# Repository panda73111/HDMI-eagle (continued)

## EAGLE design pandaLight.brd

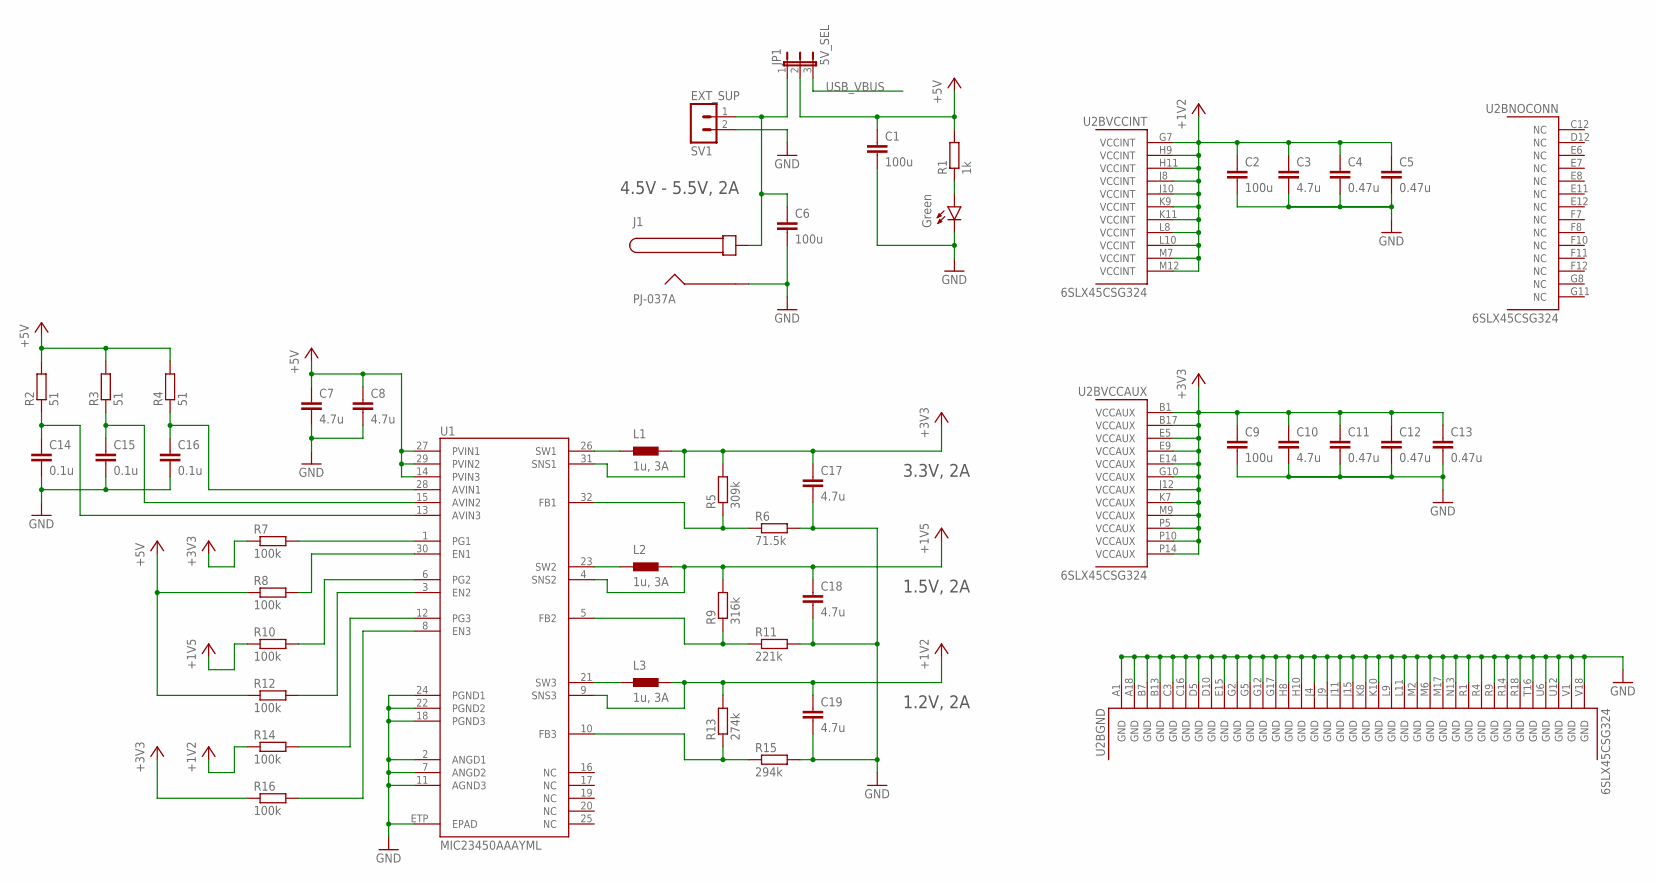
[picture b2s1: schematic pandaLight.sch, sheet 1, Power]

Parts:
C1, C2, C6, C9: 100u; 1206; PARTNO CL31A107MQHNNNE
C3, C7, C8, C10, C17, C18, C19: 4.7u; 0603; PARTNO C0603C475K9PACTU
C4, C5, C11, C12, C13: 0.47u; 0402; PARTNO C1005X5R0J474K050BB
C14, C15, C16: 0.1u; 0402; PARTNO CL05B104KP5NNNC
J1: PJ-037A; PARTNO PJ-037A
JP1: 5V_SEL; JP2; PARTNO *
L1, L2, L3: 1u, 3A; 1008; PARTNO CIG22E1R0MNE
LED1: Green; LED-0603; PARTNO LG Q971-KN-1
R1: 1k; 0402; PARTNO ERJ-2RKF1001X
R2, R3, R4: 51; 0402; PARTNO ERJ-2RKF51R0X
R5: 309k; 0402; PARTNO ERJ-2RKF3093X
R6: 71.5k; 0402; PARTNO ERJ-2RKF7152X
R7, R8, R10, R12, R14, R16: 100k; 0402; PARTNO ERJ-2RKF1003X
R9: 316k; 0402; PARTNO ERJ-2RKF3163X
R11: 221k; 0402; PARTNO ERJ-2RKF2213X
R13: 274k; 0402; PARTNO ERJ-2RKF2743X
R15: 294k; 0402; PARTNO ERJ-2RKF2943X
SV1: EXT_SUP; MA02-1; PARTNO *
U1: MIC23450AAAYML; QFN-32-5X5; PARTNO MIC23450-AAAYML TR
U2: 6SLX45CSG324; CS324; PARTNO XC6SLX45-3CSG324C

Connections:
+1V2: C2.1, C3.1, C4.1, C5.1, C19.1, L3.2, R13.2, R14.1, U1.9 (SNS3), U2.G7 (VCCINT), U2.H9 (VCCINT), U2.H11 (VCCINT), U2.J8 (VCCINT), U2.J10 (VCCINT), U2.K9 (VCCINT), U2.K11 (VCCINT), U2.L8 (VCCINT), U2.L10 (VCCINT), U2.M7 (VCCINT), U2.M12 (VCCINT)
+1V5: C18.1, L2.2, R9.2, R10.1, U1.4 (SNS2); also elsewhere on the board
+3V3: C9.1, C10.1, C11.1, C12.1, C13.1, C17.1, L1.2, R5.2, R7.1, R16.1, U1.31 (SNS1), U2.B1 (VCCAUX), U2.B17 (VCCAUX), U2.E5 (VCCAUX), U2.E9 (VCCAUX), U2.E14 (VCCAUX), U2.G10 (VCCAUX), U2.J12 (VCCAUX), U2.K7 (VCCAUX), U2.M9 (VCCAUX), U2.P5 (VCCAUX), U2.P10 (VCCAUX), U2.P14 (VCCAUX); also elsewhere on the board
+5V: C1.1, C7.1, C8.1, JP1.2, R1.2, R2.2, R3.2, R4.2, R8.1, R12.1, U1.14 (PVIN3), U1.27 (PVIN1), U1.29 (PVIN2); also elsewhere on the board
CENTER: C6.1, J1.CENTER, JP1.1, SV1.1
GND: C1.2, C2.2, C3.2, C4.2, C5.2, C6.2, C7.2, C8.2, C9.2, C10.2, C11.2, C12.2, C13.2, C14.2, C15.2, C16.2, C17.2, C18.2, C19.2, J1.BARREL, LED1.C, R6.2, R11.2, R15.2, SV1.2, U1.2 (ANGD1), U1.7 (ANGD2), U1.11 (AGND3), U1.18 (PGND3), U1.22 (PGND2), U1.24 (PGND1), U1.ETP (EPAD), U2.A1 (GND), U2.A18 (GND), U2.B7 (GND), U2.B13 (GND), U2.C3 (GND), U2.C16 (GND), U2.D5 (GND), U2.D10 (GND), U2.E15 (GND), U2.G2 (GND), U2.G5 (GND), U2.G12 (GND), U2.G17 (GND), U2.H8 (GND), U2.H10 (GND), U2.J4 (GND), U2.J9 (GND), U2.J11 (GND), U2.J15 (GND), U2.K8 (GND), U2.K10 (GND), U2.L9 (GND), U2.L11 (GND), U2.M2 (GND), U2.M6 (GND), U2.M17 (GND), U2.N13 (GND), U2.R1 (GND), U2.R4 (GND), U2.R9 (GND), U2.R14 (GND), U2.R18 (GND), U2.T16 (GND), U2.U6 (GND), U2.U12 (GND), U2.V1 (GND), U2.V18 (GND); also elsewhere on the board
unnamed: L1.1, U1.26 (SW1)
unnamed: C16.1, R4.1, U1.28 (AVIN1)
unnamed: L2.1, U1.23 (SW2)
unnamed: L3.1, U1.21 (SW3)
unnamed: R13.1, R15.1, U1.10 (FB3)
unnamed: R10.2, U1.6 (PG2)
unnamed: R5.1, R6.1, U1.32 (FB1)
unnamed: R7.2, U1.1 (PG1)
unnamed: R9.1, R11.1, U1.5 (FB2)
unnamed: R12.2, U1.3 (EN2)
unnamed: R8.2, U1.30 (EN1)
unnamed: R14.2, U1.12 (PG3)
unnamed: R16.2, U1.8 (EN3)
unnamed: C15.1, R3.1, U1.15 (AVIN2)
unnamed: LED1.A, R1.1
unnamed: C14.1, R2.1, U1.13 (AVIN3)
USB_VBUS: JP1.3; also elsewhere on the board

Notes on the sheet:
4.5V - 5.5V, 2A
3.3V, 2A
1.5V, 2A
1.2V, 2A

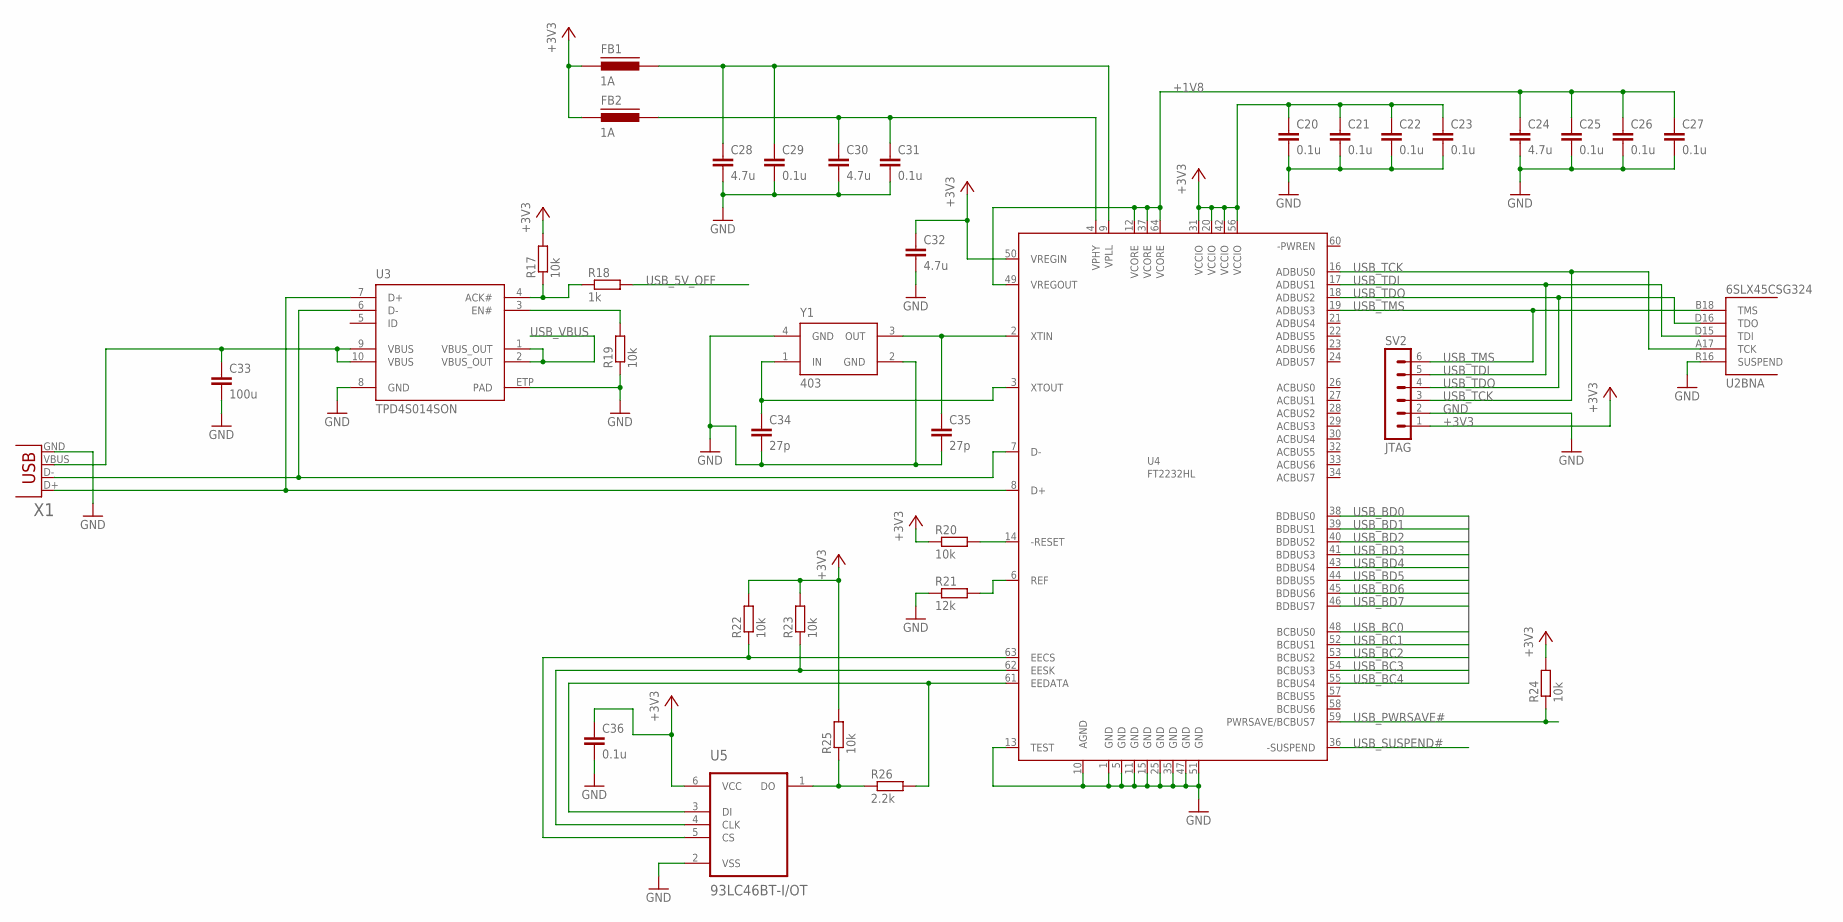
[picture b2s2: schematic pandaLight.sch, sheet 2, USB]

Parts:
C20, C21, C22, C23, C25, C26, C27, C29, C31, C36: 0.1u; 0402; PARTNO CL05B104KP5NNNC
C24, C28, C30, C32: 4.7u; 0603; PARTNO C0603C475K9PACTU
C33: 100u; 1206; PARTNO CL31A107MQHNNNE
C34, C35: 27p; 0402; PARTNO CL05C270JB5NNNC
FB1, FB2: 1A; 0402; PARTNO BK1005HS100-T
R17, R19, R20, R22, R23, R24, R25: 10k; 0402; PARTNO ERJ-2RKF1002X
R18: 1k; 0402; PARTNO ERJ-2RKF1001X
R21: 12k; 0402; PARTNO ERJ-2RKF1202X
R26: 2.2k; 0402; PARTNO ERJ-2RKF2201X
SV2: JTAG; MA06-1; PARTNO *
U2: 6SLX45CSG324; CS324; PARTNO XC6SLX45-3CSG324C
U3: TPD4S014SON; SON10; PARTNO TPD4S014DSQR
U4: FT2232HL; LQFP64; PARTNO FT2232HL-REEL
U5: 93LC46BT-I/OT; SOT23-6; PARTNO 93LC46BT-I/OT
X1: USBUB-S; USB-UB-S; PARTNO 10118192-0001LF
Y1: 403; 403-3.2X2.5; PARTNO 403C35D12M00000

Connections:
+1V8: C24.1, C25.1, C26.1, C27.1, U4.12 (VCORE), U4.37 (VCORE), U4.49 (VREGOUT), U4.64 (VCORE)
+3V3: C20.1, C21.1, C22.1, C23.1, C32.1, C36.1, FB1.1, FB2.1, R17.2, R20.1, R22.2, R23.2, R24.2, R25.2, SV2.1, U4.20 (VCCIO), U4.31 (VCCIO), U4.42 (VCCIO), U4.50 (VREGIN), U4.56 (VCCIO), U5.6 (VCC); also elsewhere on the board
GND: C20.2, C21.2, C22.2, C23.2, C24.2, C25.2, C26.2, C27.2, C28.2, C29.2, C30.2, C31.2, C32.2, C33.2, C34.2, C35.2, C36.2, R19.1, R21.1, SV2.2, U2.R16 (SUSPEND), U3.8 (GND), U3.ETP (PAD), U4.1 (GND), U4.5 (GND), U4.10 (AGND), U4.11 (GND), U4.13 (TEST), U4.15 (GND), U4.25 (GND), U4.35 (GND), U4.47 (GND), U4.51 (GND), U5.2 (VSS), X1.GND, Y1.2 (GND), Y1.4 (GND); also elsewhere on the board
unnamed: C35.1, U4.2 (XTIN), Y1.3 (OUT)
unnamed: C34.1, U4.3 (XTOUT), Y1.1 (IN)
unnamed: R22.1, U4.63 (EECS), U5.5 (CS)
unnamed: U3.6 (D-), U4.7 (D-), X1.D-
unnamed: U3.7 (D+), U4.8 (D+), X1.D+
unnamed: R23.1, U4.62 (EESK), U5.4 (CLK)
unnamed: R26.2, U4.61 (EEDATA), U5.3 (DI)
unnamed: R21.2, U4.6 (REF)
unnamed: R25.1, R26.1, U5.1 (DO)
unnamed: R20.2, U4.14 (-RESET)
unnamed: C30.1, C31.1, FB2.2, U4.4 (VPHY)
unnamed: C28.1, C29.1, FB1.2, U4.9 (VPLL)
unnamed: C33.1, U3.9 (VBUS), U3.10 (VBUS), X1.VBUS
USB_5V_ACK#: R17.1, R18.1, U3.4 (ACK#)
USB_5V_DISABLE: R19.2, U3.3 (EN#)
USB_5V_OFF: R18.2
USB_BC0: U4.48 (BCBUS0)
USB_BC1: U4.52 (BCBUS1)
USB_BC2: U4.53 (BCBUS2)
USB_BC3: U4.54 (BCBUS3)
USB_BC4: U4.55 (BCBUS4)
USB_BD0: U4.38 (BDBUS0)
USB_BD1: U4.39 (BDBUS1)
USB_BD2: U4.40 (BDBUS2)
USB_BD3: U4.41 (BDBUS3)
USB_BD4: U4.43 (BDBUS4)
USB_BD5: U4.44 (BDBUS5)
USB_BD6: U4.45 (BDBUS6)
USB_BD7: U4.46 (BDBUS7)
USB_PWRSAVE#: R24.1, U4.59 (PWRSAVE/BCBUS7)
USB_SUSPEND#: U4.36 (-SUSPEND)
USB_TCK: SV2.3, U2.A17 (TCK), U4.16 (ADBUS0)
USB_TDI: SV2.5, U2.D15 (TDI), U4.17 (ADBUS1)
USB_TDO: SV2.4, U2.D16 (TDO), U4.18 (ADBUS2)
USB_TMS: SV2.6, U2.B18 (TMS), U4.19 (ADBUS3)
USB_VBUS: U3.1 (VBUS_OUT), U3.2 (VBUS_OUT); also elsewhere on the board

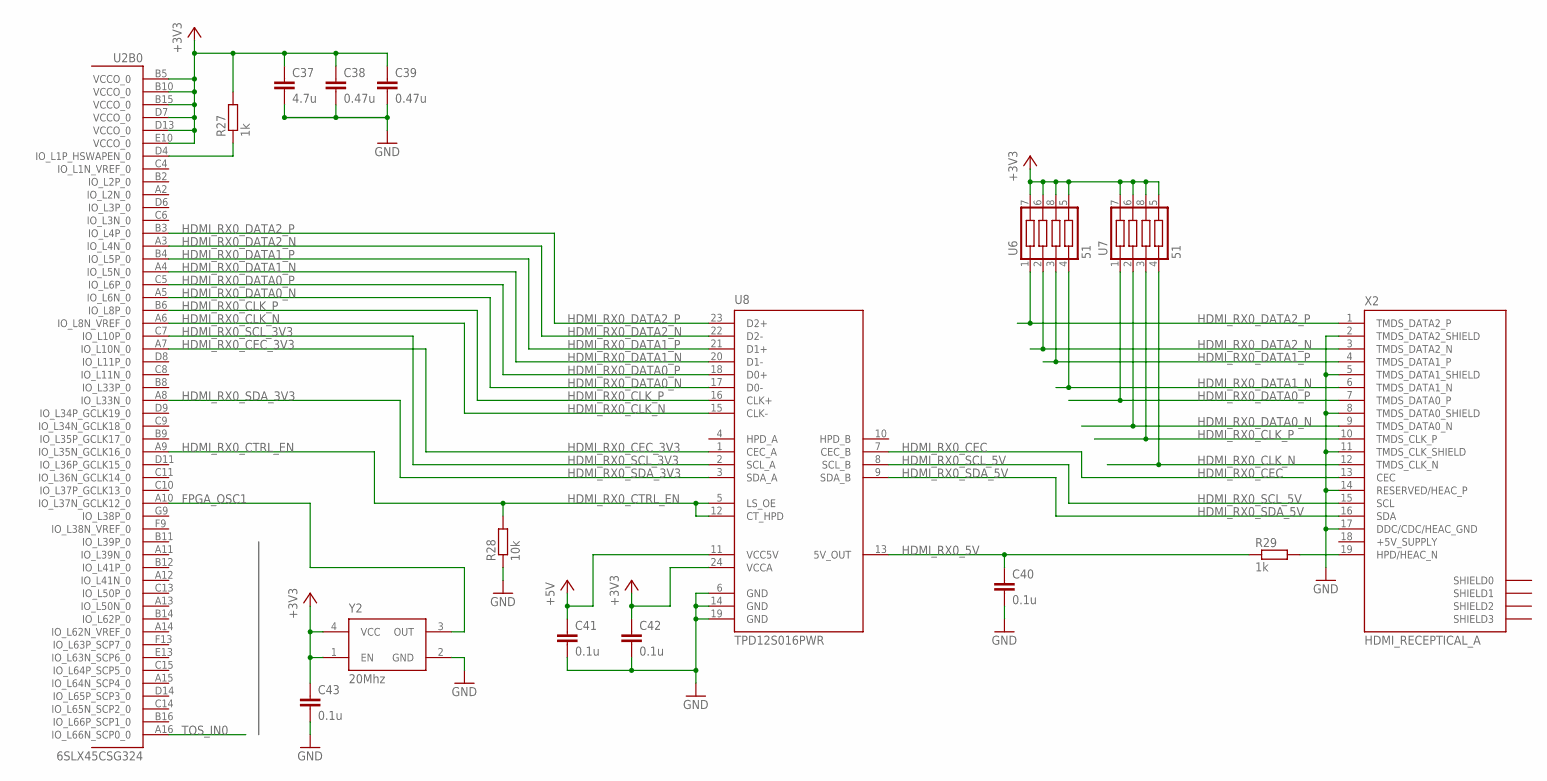
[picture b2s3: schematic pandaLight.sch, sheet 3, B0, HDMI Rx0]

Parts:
C37: 4.7u; 0603; PARTNO C0603C475K9PACTU
C38, C39: 0.47u; 0402; PARTNO C1005X5R0J474K050BB
C40, C41, C42, C43: 0.1u; 0402; PARTNO CL05B104KP5NNNC
R27, R29: 1k; 0402; PARTNO ERJ-2RKF1001X
R28: 10k; 0402; PARTNO ERJ-2RKF1002X
U2: 6SLX45CSG324; CS324; PARTNO XC6SLX45-3CSG324C
U6, U7: 51; 741C083; PARTNO 741C083510JP
U8: TPD12S016PWR; PW_R-PDSO-G24; PARTNO TPD12S016PWR
X2: HDMI_RECEPTICAL_A; HDMI_TYPE_A_RECEPTICAL; PARTNO 10029449-111RLF
Y2: 20Mhz; 636; PARTNO 636L3C020M00000

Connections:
+3V3: C37.1, C38.1, C39.1, C42.1, C43.1, R27.2, U2.B5 (VCCO_0), U2.B10 (VCCO_0), U2.B15 (VCCO_0), U2.D7 (VCCO_0), U2.D13 (VCCO_0), U2.E10 (VCCO_0), U6.5 (13), U6.6 (15), U6.7 (16), U6.8 (C3), U7.5 (13), U7.6 (15), U7.7 (16), U7.8 (C3), U8.24 (VCCA), Y2.1 (EN), Y2.4 (VCC); also elsewhere on the board
+5V: C41.1, U8.11 (VCC5V); also elsewhere on the board
FPGA_OSC1: U2.A10 (IO_L37N_GCLK12_0), Y2.3 (OUT)
GND: C37.2, C38.2, C39.2, C40.2, C41.2, C42.2, C43.2, R28.1, U8.6 (GND), U8.14 (GND), U8.19 (GND), X2.2 (TMDS_DATA2_SHIELD), X2.5 (TMDS_DATA1_SHIELD), X2.8 (TMDS_DATA0_SHIELD), X2.11 (TMDS_CLK_SHIELD), X2.14 (RESERVED/HEAC_P), X2.17 (DDC/CDC/HEAC_GND), Y2.2 (GND); also elsewhere on the board
HDMI_RX0_5V: C40.1, R29.1, U8.13 (5V_OUT)
HDMI_RX0_CEC: U8.7 (CEC_B), X2.13 (CEC)
HDMI_RX0_CEC_3V3: U2.A7 (IO_L10N_0), U8.1 (CEC_A)
HDMI_RX0_CLK_N: U2.A6 (IO_L8N_VREF_0), U7.4, U8.15 (CLK-), X2.12 (TMDS_CLK_N)
HDMI_RX0_CLK_P: U2.B6 (IO_L8P_0), U7.3, U8.16 (CLK+), X2.10 (TMDS_CLK_P)
HDMI_RX0_CTRL_EN: R28.2, U2.A9 (IO_L35N_GCLK16_0), U8.5 (LS_OE), U8.12 (CT_HPD)
HDMI_RX0_DATA0_N: U2.A5 (IO_L6N_0), U7.2, U8.17 (D0-), X2.9 (TMDS_DATA0_N)
HDMI_RX0_DATA0_P: U2.C5 (IO_L6P_0), U7.1, U8.18 (D0+), X2.7 (TMDS_DATA0_P)
HDMI_RX0_DATA1_N: U2.A4 (IO_L5N_0), U6.4, U8.20 (D1-), X2.6 (TMDS_DATA1_N)
HDMI_RX0_DATA1_P: U2.B4 (IO_L5P_0), U6.3, U8.21 (D1+), X2.4 (TMDS_DATA1_P)
HDMI_RX0_DATA2_N: U2.A3 (IO_L4N_0), U6.2, U8.22 (D2-), X2.3 (TMDS_DATA2_N)
HDMI_RX0_DATA2_P: U2.B3 (IO_L4P_0), U6.1, U8.23 (D2+), X2.1 (TMDS_DATA2_P)
HDMI_RX0_SCL_3V3: U2.C7 (IO_L10P_0), U8.2 (SCL_A)
HDMI_RX0_SCL_5V: U8.8 (SCL_B), X2.15 (SCL)
HDMI_RX0_SDA_3V3: U2.A8 (IO_L33N_0), U8.3 (SDA_A)
HDMI_RX0_SDA_5V: U8.9 (SDA_B), X2.16 (SDA)
unnamed: R27.1, U2.D4 (IO_L1P_HSWAPEN_0)
unnamed: R29.2, X2.19 (HPD/HEAC_N)
TOS_IN0: U2.A16 (IO_L66N_SCP0_0); also elsewhere on the board

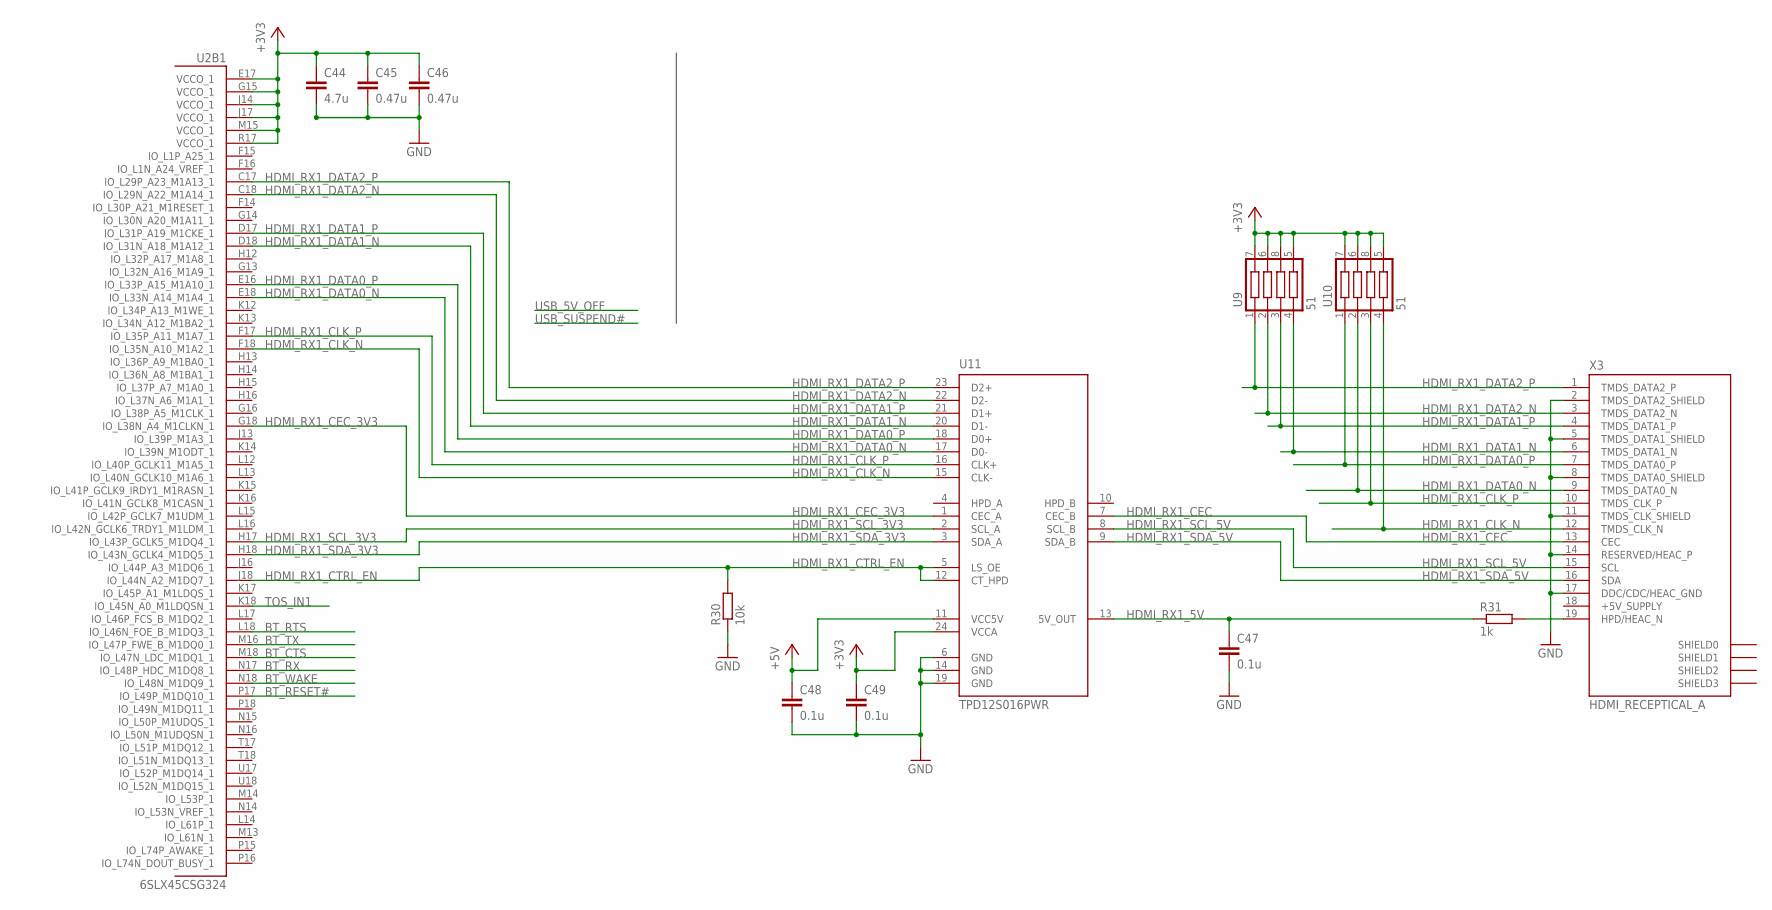
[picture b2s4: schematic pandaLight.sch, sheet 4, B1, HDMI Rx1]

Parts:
C44: 4.7u; 0603; PARTNO C0603C475K9PACTU
C45, C46: 0.47u; 0402; PARTNO C1005X5R0J474K050BB
C47, C48, C49: 0.1u; 0402; PARTNO CL05B104KP5NNNC
R30: 10k; 0402; PARTNO ERJ-2RKF1002X
R31: 1k; 0402; PARTNO ERJ-2RKF1001X
U2: 6SLX45CSG324; CS324; PARTNO XC6SLX45-3CSG324C
U9, U10: 51; 741C083; PARTNO 741C083510JP
U11: TPD12S016PWR; PW_R-PDSO-G24; PARTNO TPD12S016PWR
X3: HDMI_RECEPTICAL_A; HDMI_TYPE_A_RECEPTICAL; PARTNO 10029449-111RLF

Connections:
+3V3: C44.1, C45.1, C46.1, C49.1, U2.E17 (VCCO_1), U2.G15 (VCCO_1), U2.J14 (VCCO_1), U2.J17 (VCCO_1), U2.M15 (VCCO_1), U2.R17 (VCCO_1), U9.5 (13), U9.6 (15), U9.7 (16), U9.8 (C3), U10.5 (13), U10.6 (15), U10.7 (16), U10.8 (C3), U11.24 (VCCA); also elsewhere on the board
+5V: C48.1, U11.11 (VCC5V); also elsewhere on the board
BT_CTS: U2.M18 (IO_L47N_LDC_M1DQ1_1); also elsewhere on the board
BT_RESET#: U2.P17 (IO_L49P_M1DQ10_1); also elsewhere on the board
BT_RTS: U2.L18 (IO_L46N_FOE_B_M1DQ3_1); also elsewhere on the board
BT_RX: U2.N17 (IO_L48P_HDC_M1DQ8_1); also elsewhere on the board
BT_TX: U2.M16 (IO_L47P_FWE_B_M1DQ0_1); also elsewhere on the board
BT_WAKE: U2.N18 (IO_L48N_M1DQ9_1); also elsewhere on the board
GND: C44.2, C45.2, C46.2, C47.2, C48.2, C49.2, R30.1, U11.6 (GND), U11.14 (GND), U11.19 (GND), X3.2 (TMDS_DATA2_SHIELD), X3.5 (TMDS_DATA1_SHIELD), X3.8 (TMDS_DATA0_SHIELD), X3.11 (TMDS_CLK_SHIELD), X3.14 (RESERVED/HEAC_P), X3.17 (DDC/CDC/HEAC_GND); also elsewhere on the board
HDMI_RX1_5V: C47.1, R31.1, U11.13 (5V_OUT)
HDMI_RX1_CEC: U11.7 (CEC_B), X3.13 (CEC)
HDMI_RX1_CEC_3V3: U2.G18 (IO_L38N_A4_M1CLKN_1), U11.1 (CEC_A)
HDMI_RX1_CLK_N: U2.F18 (IO_L35N_A10_M1A2_1), U10.4, U11.15 (CLK-), X3.12 (TMDS_CLK_N)
HDMI_RX1_CLK_P: U2.F17 (IO_L35P_A11_M1A7_1), U10.3, U11.16 (CLK+), X3.10 (TMDS_CLK_P)
HDMI_RX1_CTRL_EN: R30.2, U2.J18 (IO_L44N_A2_M1DQ7_1), U11.5 (LS_OE), U11.12 (CT_HPD)
HDMI_RX1_DATA0_N: U2.E18 (IO_L33N_A14_M1A4_1), U10.2, U11.17 (D0-), X3.9 (TMDS_DATA0_N)
HDMI_RX1_DATA0_P: U2.E16 (IO_L33P_A15_M1A10_1), U10.1, U11.18 (D0+), X3.7 (TMDS_DATA0_P)
HDMI_RX1_DATA1_N: U2.D18 (IO_L31N_A18_M1A12_1), U9.4, U11.20 (D1-), X3.6 (TMDS_DATA1_N)
HDMI_RX1_DATA1_P: U2.D17 (IO_L31P_A19_M1CKE_1), U9.3, U11.21 (D1+), X3.4 (TMDS_DATA1_P)
HDMI_RX1_DATA2_N: U2.C18 (IO_L29N_A22_M1A14_1), U9.2, U11.22 (D2-), X3.3 (TMDS_DATA2_N)
HDMI_RX1_DATA2_P: U2.C17 (IO_L29P_A23_M1A13_1), U9.1, U11.23 (D2+), X3.1 (TMDS_DATA2_P)
HDMI_RX1_SCL_3V3: U2.H17 (IO_L43P_GCLK5_M1DQ4_1), U11.2 (SCL_A)
HDMI_RX1_SCL_5V: U11.8 (SCL_B), X3.15 (SCL)
HDMI_RX1_SDA_3V3: U2.H18 (IO_L43N_GCLK4_M1DQ5_1), U11.3 (SDA_A)
HDMI_RX1_SDA_5V: U11.9 (SDA_B), X3.16 (SDA)
unnamed: R31.2, X3.19 (HPD/HEAC_N)
TOS_IN1: U2.K18 (IO_L45N_A0_M1LDQSN_1); also elsewhere on the board

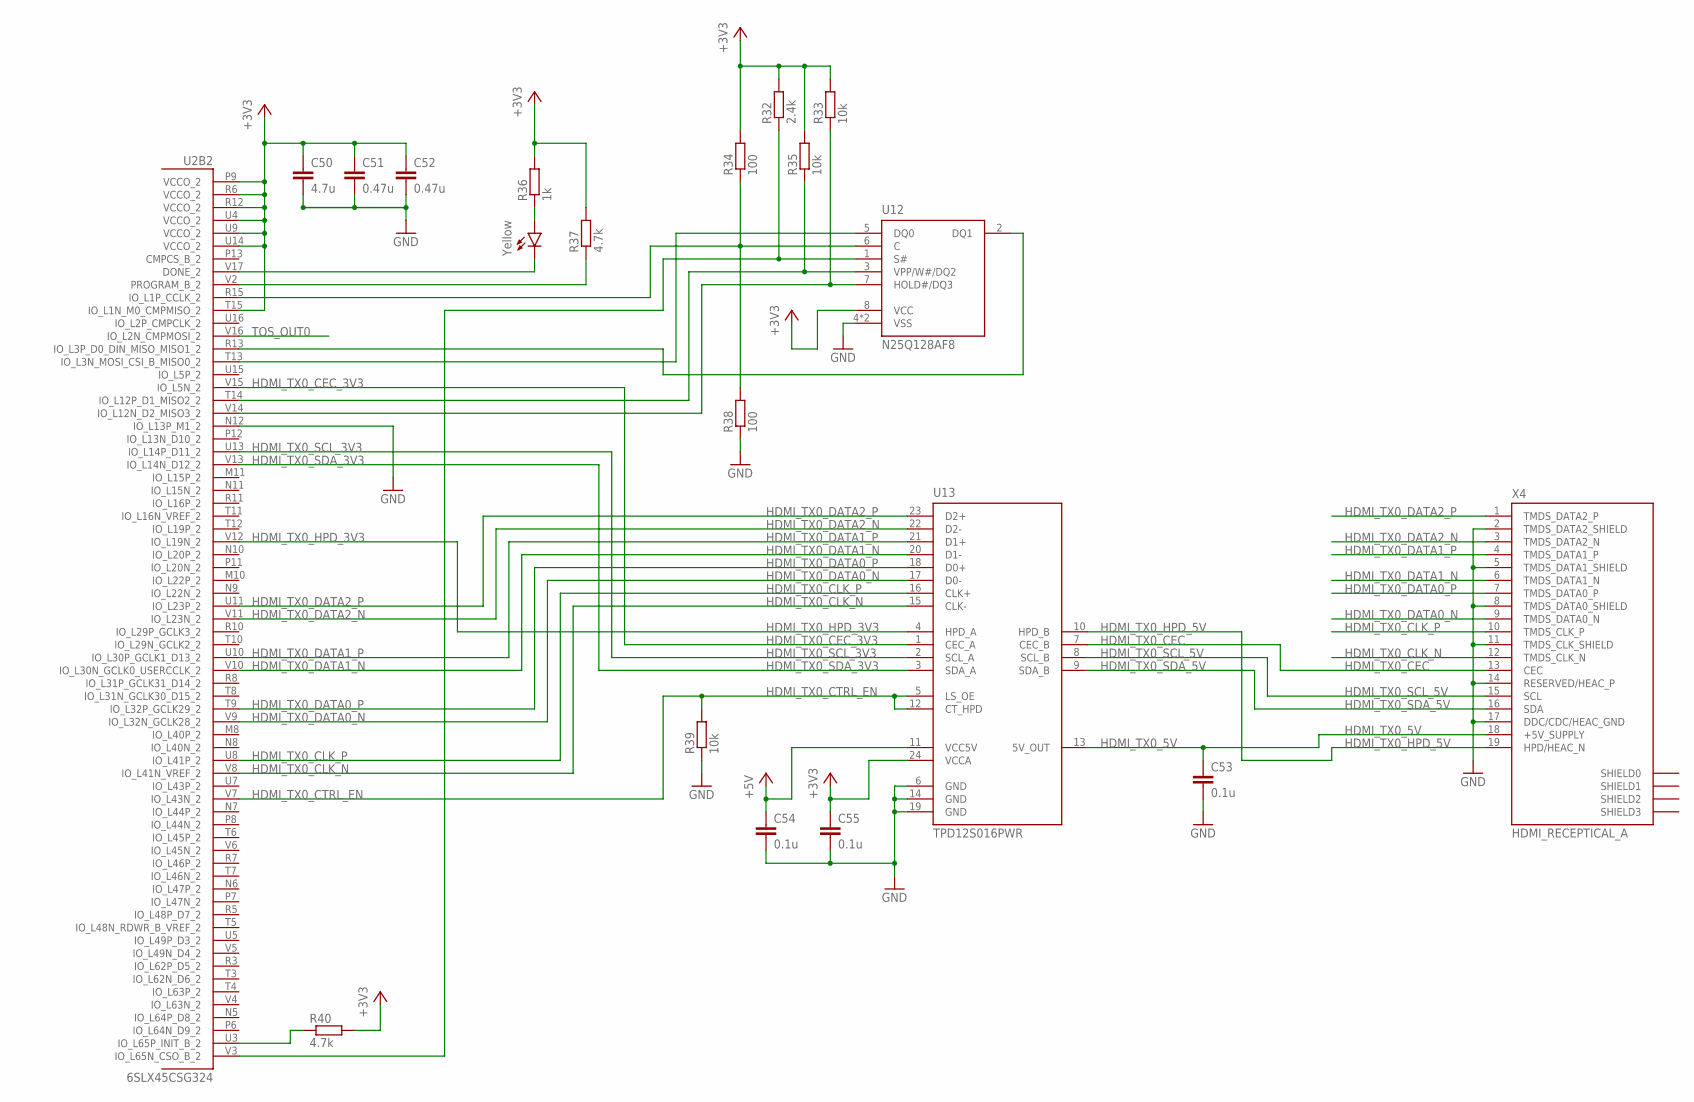
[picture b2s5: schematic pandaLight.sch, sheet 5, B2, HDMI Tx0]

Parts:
C50: 4.7u; 0603; PARTNO C0603C475K9PACTU
C51, C52: 0.47u; 0402; PARTNO C1005X5R0J474K050BB
C53, C54, C55: 0.1u; 0402; PARTNO CL05B104KP5NNNC
LED2: Yellow; LED-0603; PARTNO LY Q976-P1S2-36
R32: 2.4k; 0402; PARTNO ERJ-2RKF2401X
R33, R35, R39: 10k; 0402; PARTNO ERJ-2RKF1002X
R34, R38: 100; 0402; PARTNO ERJ-2GEJ101X
R36: 1k; 0402; PARTNO ERJ-2RKF1001X
R37, R40: 4.7k; 0402; PARTNO ERJ-2RKF4701X
U2: 6SLX45CSG324; CS324; PARTNO XC6SLX45-3CSG324C
U12: N25Q128AF8; V-PDFN-8_8X6; PARTNO N25Q128A13EF840E
U13: TPD12S016PWR; PW_R-PDSO-G24; PARTNO TPD12S016PWR
X4: HDMI_RECEPTICAL_A; HDMI_TYPE_A_RECEPTICAL; PARTNO 10029449-111RLF

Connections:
+3V3: C50.1, C51.1, C52.1, C55.1, R32.2, R33.2, R34.2, R35.2, R36.2, R37.2, R40.2, U2.P9 (VCCO_2), U2.R6 (VCCO_2), U2.R12 (VCCO_2), U2.T15 (IO_L1N_M0_CMPMISO_2), U2.U4 (VCCO_2), U2.U9 (VCCO_2), U2.U14 (VCCO_2), U12.8 (VCC), U13.24 (VCCA); also elsewhere on the board
+5V: C54.1, U13.11 (VCC5V); also elsewhere on the board
GND: C50.2, C51.2, C52.2, C53.2, C54.2, C55.2, R38.1, R39.1, U2.N12 (IO_L13P_M1_2), U12.4 (VSS), U12.ETP (VSS), U13.6 (GND), U13.14 (GND), U13.19 (GND), X4.2 (TMDS_DATA2_SHIELD), X4.5 (TMDS_DATA1_SHIELD), X4.8 (TMDS_DATA0_SHIELD), X4.11 (TMDS_CLK_SHIELD), X4.14 (RESERVED/HEAC_P), X4.17 (DDC/CDC/HEAC_GND); also elsewhere on the board
HDMI_TX0_5V: C53.1, U13.13 (5V_OUT), X4.18 (+5V_SUPPLY)
HDMI_TX0_CEC: U13.7 (CEC_B), X4.13 (CEC)
HDMI_TX0_CEC_3V3: U2.V15 (IO_L5N_2), U13.1 (CEC_A)
HDMI_TX0_CLK_N: U2.V8 (IO_L41N_VREF_2), U13.15 (CLK-), X4.12 (TMDS_CLK_N)
HDMI_TX0_CLK_P: U2.U8 (IO_L41P_2), U13.16 (CLK+), X4.10 (TMDS_CLK_P)
HDMI_TX0_CTRL_EN: R39.2, U2.V7 (IO_L43N_2), U13.5 (LS_OE), U13.12 (CT_HPD)
HDMI_TX0_DATA0_N: U2.V9 (IO_L32N_GCLK28_2), U13.17 (D0-), X4.9 (TMDS_DATA0_N)
HDMI_TX0_DATA0_P: U2.T9 (IO_L32P_GCLK29_2), U13.18 (D0+), X4.7 (TMDS_DATA0_P)
HDMI_TX0_DATA1_N: U2.V10 (IO_L30N_GCLK0_USERCCLK_2), U13.20 (D1-), X4.6 (TMDS_DATA1_N)
HDMI_TX0_DATA1_P: U2.U10 (IO_L30P_GCLK1_D13_2), U13.21 (D1+), X4.4 (TMDS_DATA1_P)
HDMI_TX0_DATA2_N: U2.V11 (IO_L23N_2), U13.22 (D2-), X4.3 (TMDS_DATA2_N)
HDMI_TX0_DATA2_P: U2.U11 (IO_L23P_2), U13.23 (D2+), X4.1 (TMDS_DATA2_P)
HDMI_TX0_HPD_3V3: U2.V12 (IO_L19N_2), U13.4 (HPD_A)
HDMI_TX0_HPD_5V: U13.10 (HPD_B), X4.19 (HPD/HEAC_N)
HDMI_TX0_SCL_3V3: U2.U13 (IO_L14P_D11_2), U13.2 (SCL_A)
HDMI_TX0_SCL_5V: U13.8 (SCL_B), X4.15 (SCL)
HDMI_TX0_SDA_3V3: U2.V13 (IO_L14N_D12_2), U13.3 (SDA_A)
HDMI_TX0_SDA_5V: U13.9 (SDA_B), X4.16 (SDA)
unnamed: LED2.C, U2.V17 (DONE_2)
unnamed: R37.1, U2.V2 (PROGRAM_B_2)
unnamed: LED2.A, R36.1
unnamed: R40.1, U2.U3 (IO_L65P_INIT_B_2)
unnamed: U2.T13 (IO_L3N_MOSI_CSI_B_MISO0_2), U12.5 (DQ0)
unnamed: R32.1, U2.V3 (IO_L65N_CSO_B_2), U12.1 (S#)
unnamed: R34.1, R38.2, U2.R15 (IO_L1P_CCLK_2), U12.6 (C)
unnamed: U2.R13 (IO_L3P_D0_DIN_MISO_MISO1_2), U12.2 (DQ1)
unnamed: R35.1, U2.T14 (IO_L12P_D1_MISO2_2), U12.3 (VPP/W#/DQ2)
unnamed: R33.1, U2.V14 (IO_L12N_D2_MISO3_2), U12.7 (HOLD#/DQ3)
TOS_OUT0: U2.V16 (IO_L2N_CMPMOSI_2); also elsewhere on the board

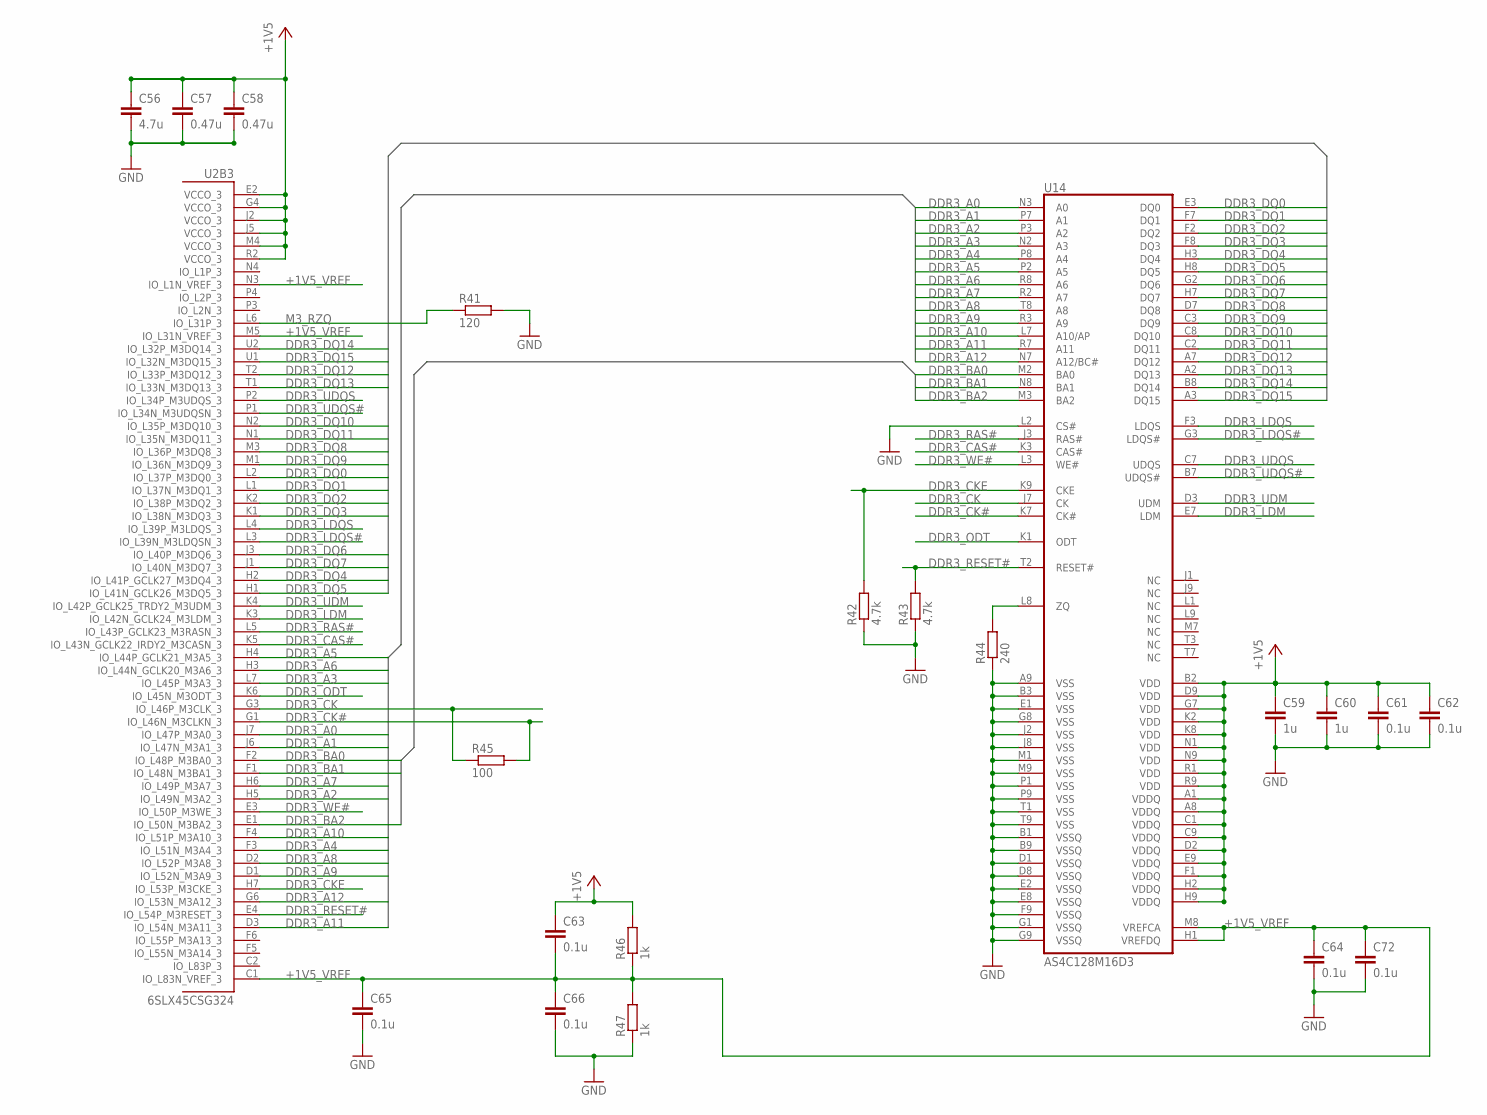
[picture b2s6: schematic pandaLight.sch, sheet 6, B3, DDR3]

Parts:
C56: 4.7u; 0603; PARTNO C0603C475K9PACTU
C57, C58: 0.47u; 0402; PARTNO C1005X5R0J474K050BB
C59, C60: 1u; 0402; PARTNO C1005X5R0J105M050BB
C61, C62, C63, C64, C65, C66, C72: 0.1u; 0402; PARTNO CL05B104KP5NNNC
R41: 120; 0402; PARTNO ERJ-2RKF1200X
R42, R43: 4.7k; 0402; PARTNO ERJ-2RKF4701X
R44: 240; 0402; PARTNO ERJ-2RKF2400X
R45: 100; 0402; PARTNO ERJ-2GEJ101X
R46, R47: 1k; 0402; PARTNO ERJ-2RKF1001X
U2: 6SLX45CSG324; CS324; PARTNO XC6SLX45-3CSG324C
U14: AS4C128M16D3; 96-FBGA_13X9; PARTNO AS4C128M16D3-12BCN

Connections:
+1V5: C56.1, C57.1, C58.1, C59.1, C60.1, C61.1, C62.1, C63.1, R46.2, U2.E2 (VCCO_3), U2.G4 (VCCO_3), U2.J2 (VCCO_3), U2.J5 (VCCO_3), U2.M4 (VCCO_3), U2.R2 (VCCO_3), U14.A1 (VDDQ), U14.A8 (VDDQ), U14.B2 (VDD), U14.C1 (VDDQ), U14.C9 (VDDQ), U14.D2 (VDDQ), U14.D9 (VDD), U14.E9 (VDDQ), U14.F1 (VDDQ), U14.G7 (VDD), U14.H2 (VDDQ), U14.H9 (VDDQ), U14.K2 (VDD), U14.K8 (VDD), U14.N1 (VDD), U14.N9 (VDD), U14.R1 (VDD), U14.R9 (VDD); also elsewhere on the board
+1V5_VREF: C63.2, C64.1, C65.1, C66.1, C72.1, R46.1, R47.2, U2.C1 (IO_L83N_VREF_3), U2.M5 (IO_L31N_VREF_3), U2.N3 (IO_L1N_VREF_3), U14.H1 (VREFDQ), U14.M8 (VREFCA)
DDR3_A0: U2.J7 (IO_L47P_M3A0_3), U14.N3 (A0)
DDR3_A1: U2.J6 (IO_L47N_M3A1_3), U14.P7 (A1)
DDR3_A2: U2.H5 (IO_L49N_M3A2_3), U14.P3 (A2)
DDR3_A3: U2.L7 (IO_L45P_M3A3_3), U14.N2 (A3)
DDR3_A4: U2.F3 (IO_L51N_M3A4_3), U14.P8 (A4)
DDR3_A5: U2.H4 (IO_L44P_GCLK21_M3A5_3), U14.P2 (A5)
DDR3_A6: U2.H3 (IO_L44N_GCLK20_M3A6_3), U14.R8 (A6)
DDR3_A7: U2.H6 (IO_L49P_M3A7_3), U14.R2 (A7)
DDR3_A8: U2.D2 (IO_L52P_M3A8_3), U14.T8 (A8)
DDR3_A9: U2.D1 (IO_L52N_M3A9_3), U14.R3 (A9)
DDR3_A10: U2.F4 (IO_L51P_M3A10_3), U14.L7 (A10/AP)
DDR3_A11: U2.D3 (IO_L54N_M3A11_3), U14.R7 (A11)
DDR3_A12: U2.G6 (IO_L53N_M3A12_3), U14.N7 (A12/BC#)
DDR3_BA0: U2.F2 (IO_L48P_M3BA0_3), U14.M2 (BA0)
DDR3_BA1: U2.F1 (IO_L48N_M3BA1_3), U14.N8 (BA1)
DDR3_BA2: U2.E1 (IO_L50N_M3BA2_3), U14.M3 (BA2)
DDR3_CAS#: U2.K5 (IO_L43N_GCLK22_IRDY2_M3CASN_3), U14.K3 (CAS#)
DDR3_CK: R45.1, U2.G3 (IO_L46P_M3CLK_3), U14.J7 (CK)
DDR3_CK#: R45.2, U2.G1 (IO_L46N_M3CLKN_3), U14.K7 (CK#)
DDR3_CKE: R42.2, U2.H7 (IO_L53P_M3CKE_3), U14.K9 (CKE)
DDR3_DQ0: U2.L2 (IO_L37P_M3DQ0_3), U14.E3 (DQ0)
DDR3_DQ1: U2.L1 (IO_L37N_M3DQ1_3), U14.F7 (DQ1)
DDR3_DQ2: U2.K2 (IO_L38P_M3DQ2_3), U14.F2 (DQ2)
DDR3_DQ3: U2.K1 (IO_L38N_M3DQ3_3), U14.F8 (DQ3)
DDR3_DQ4: U2.H2 (IO_L41P_GCLK27_M3DQ4_3), U14.H3 (DQ4)
DDR3_DQ5: U2.H1 (IO_L41N_GCLK26_M3DQ5_3), U14.H8 (DQ5)
DDR3_DQ6: U2.J3 (IO_L40P_M3DQ6_3), U14.G2 (DQ6)
DDR3_DQ7: U2.J1 (IO_L40N_M3DQ7_3), U14.H7 (DQ7)
DDR3_DQ8: U2.M3 (IO_L36P_M3DQ8_3), U14.D7 (DQ8)
DDR3_DQ9: U2.M1 (IO_L36N_M3DQ9_3), U14.C3 (DQ9)
DDR3_DQ10: U2.N2 (IO_L35P_M3DQ10_3), U14.C8 (DQ10)
DDR3_DQ11: U2.N1 (IO_L35N_M3DQ11_3), U14.C2 (DQ11)
DDR3_DQ12: U2.T2 (IO_L33P_M3DQ12_3), U14.A7 (DQ12)
DDR3_DQ13: U2.T1 (IO_L33N_M3DQ13_3), U14.A2 (DQ13)
DDR3_DQ14: U2.U2 (IO_L32P_M3DQ14_3), U14.B8 (DQ14)
DDR3_DQ15: U2.U1 (IO_L32N_M3DQ15_3), U14.A3 (DQ15)
DDR3_LDM: U2.K3 (IO_L42N_GCLK24_M3LDM_3), U14.E7 (LDM)
DDR3_LDQS: U2.L4 (IO_L39P_M3LDQS_3), U14.F3 (LDQS)
DDR3_LDQS#: U2.L3 (IO_L39N_M3LDQSN_3), U14.G3 (LDQS#)
DDR3_ODT: U2.K6 (IO_L45N_M3ODT_3), U14.K1 (ODT)
DDR3_RAS#: U2.L5 (IO_L43P_GCLK23_M3RASN_3), U14.J3 (RAS#)
DDR3_RESET#: R43.2, U2.E4 (IO_L54P_M3RESET_3), U14.T2 (RESET#)
DDR3_UDM: U2.K4 (IO_L42P_GCLK25_TRDY2_M3UDM_3), U14.D3 (UDM)
DDR3_UDQS: U2.P2 (IO_L34P_M3UDQS_3), U14.C7 (UDQS)
DDR3_UDQS#: U2.P1 (IO_L34N_M3UDQSN_3), U14.B7 (UDQS#)
DDR3_WE#: U2.E3 (IO_L50P_M3WE_3), U14.L3 (WE#)
GND: C56.2, C57.2, C58.2, C59.2, C60.2, C61.2, C62.2, C64.2, C65.2, C66.2, C72.2, R41.2, R42.1, R43.1, R44.1, R47.1, U14.A9 (VSS), U14.B1 (VSSQ), U14.B3 (VSS), U14.B9 (VSSQ), U14.D1 (VSSQ), U14.D8 (VSSQ), U14.E1 (VSS), U14.E2 (VSSQ), U14.E8 (VSSQ), U14.F9 (VSSQ), U14.G1 (VSSQ), U14.G8 (VSS), U14.G9 (VSSQ), U14.J2 (VSS), U14.J8 (VSS), U14.L2 (CS#), U14.M1 (VSS), U14.M9 (VSS), U14.P1 (VSS), U14.P9 (VSS), U14.T1 (VSS), U14.T9 (VSS); also elsewhere on the board
M3_RZQ: R41.1, U2.L6 (IO_L31P_3)
unnamed: R44.2, U14.L8 (ZQ)

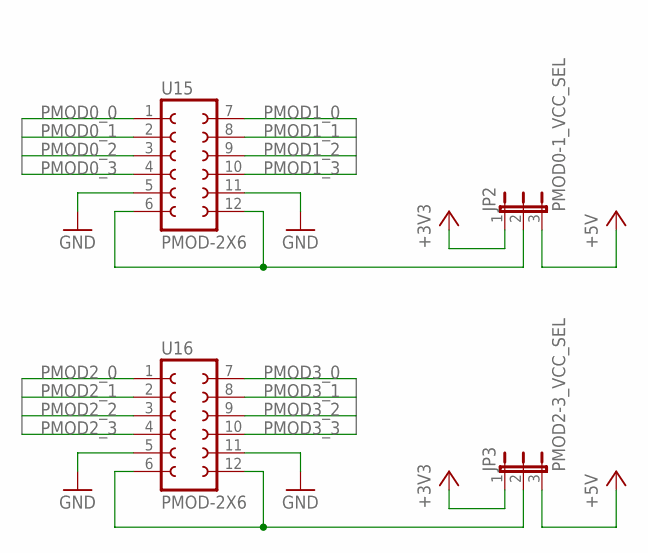
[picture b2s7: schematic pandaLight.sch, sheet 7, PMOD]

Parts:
JP2: PMOD0-1_VCC_SEL; JP2; PARTNO *
JP3: PMOD2-3_VCC_SEL; JP2; PARTNO *
U15, U16: PMOD-2X6; PARTNO PPTC062LJBN-RC

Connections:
+3V3: JP2.1, JP3.1; also elsewhere on the board
+5V: JP2.3, JP3.3; also elsewhere on the board
GND: U15.5, U15.11, U16.5, U16.11; also elsewhere on the board
unnamed: JP3.2, U16.6, U16.12
unnamed: JP2.2, U15.6, U15.12
PMOD0_0: U15.1
PMOD0_1: U15.2
PMOD0_2: U15.3
PMOD0_3: U15.4
PMOD1_0: U15.7
PMOD1_1: U15.8
PMOD1_2: U15.9
PMOD1_3: U15.10
PMOD2_0: U16.1
PMOD2_1: U16.2
PMOD2_2: U16.3
PMOD2_3: U16.4
PMOD3_0: U16.7
PMOD3_1: U16.8
PMOD3_2: U16.9
PMOD3_3: U16.10

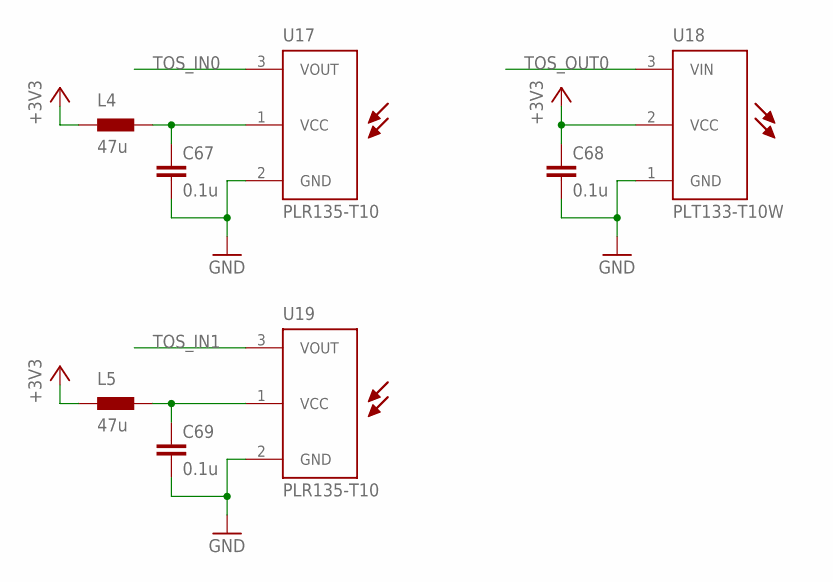
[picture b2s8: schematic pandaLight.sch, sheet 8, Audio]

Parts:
C67, C68, C69: 0.1u; 0402; PARTNO CL05B104KP5NNNC
L4, L5: 47u; 0603; PARTNO GLFR1608T470M-LR
U17, U19: PLR135-T10; PLR135-T10_PLT133-T10W; PARTNO PLR135/T10
U18: PLT133-T10W; PLR135-T10_PLT133-T10W; PARTNO PLT133/T10W

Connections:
+3V3: C68.1, L4.1, L5.1, U18.2 (VCC); also elsewhere on the board
GND: C67.2, C68.2, C69.2, U17.2 (GND), U18.1 (GND), U19.2 (GND); also elsewhere on the board
unnamed: C69.1, L5.2, U19.1 (VCC)
unnamed: C67.1, L4.2, U17.1 (VCC)
TOS_IN0: U17.3 (VOUT); also elsewhere on the board
TOS_IN1: U19.3 (VOUT); also elsewhere on the board
TOS_OUT0: U18.3 (VIN); also elsewhere on the board

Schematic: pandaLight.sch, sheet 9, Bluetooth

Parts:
C70, C71: 0.1u; 0402; PARTNO CL05B104KP5NNNC
R48, R49: 10k; 0402; PARTNO ERJ-2RKF1002X
U20, U21: TP10SQ; PARTNO *
U22: PAN1322; PARTNO ENW-89841A3KF

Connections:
+3V3: C70.1, C71.1, R48.2, U22.A4 (VSUPPLY), U22.A5 (VSUPPLY), U22.A6 (VSUPPLY), U22.B5 (ONOFF), U22.C5 (VDD1), U22.F6 (VDDUART); also elsewhere on the board
BT_CTS: U22.F5 (P0.7_UARTCTS); also elsewhere on the board
BT_RESET#: R49.2, U22.A3 (RESET#); also elsewhere on the board
BT_RTS: U22.F8 (P0.6_UARTRTS); also elsewhere on the board
BT_RX: U22.E6 (P0.5_UARTRXD); also elsewhere on the board
BT_TX: U22.F7 (P0.4_UARTTXD); also elsewhere on the board
BT_WAKE: R48.1, U22.F4 (P0.14_LPMIN); also elsewhere on the board
GND: C70.2, C71.2, R49.1, U22.A1 (VSS), U22.A7 (VSS), U22.A9 (VSS), U22.A11 (VSS), U22.A12 (VSS), U22.C8 (VSS), U22.C9 (VSS), U22.D7 (VSS), U22.D8 (VSS), U22.E8 (VSS), U22.E9 (VSS), U22.F1 (VSS), U22.F9 (VSS), U22.F11 (VSS), U22.F12 (VSS); also elsewhere on the board
unnamed: U21.TP, U22.E1 (P0.12_SDA0)
unnamed: U20.TP, U22.E2 (P0.13_SCL0)
